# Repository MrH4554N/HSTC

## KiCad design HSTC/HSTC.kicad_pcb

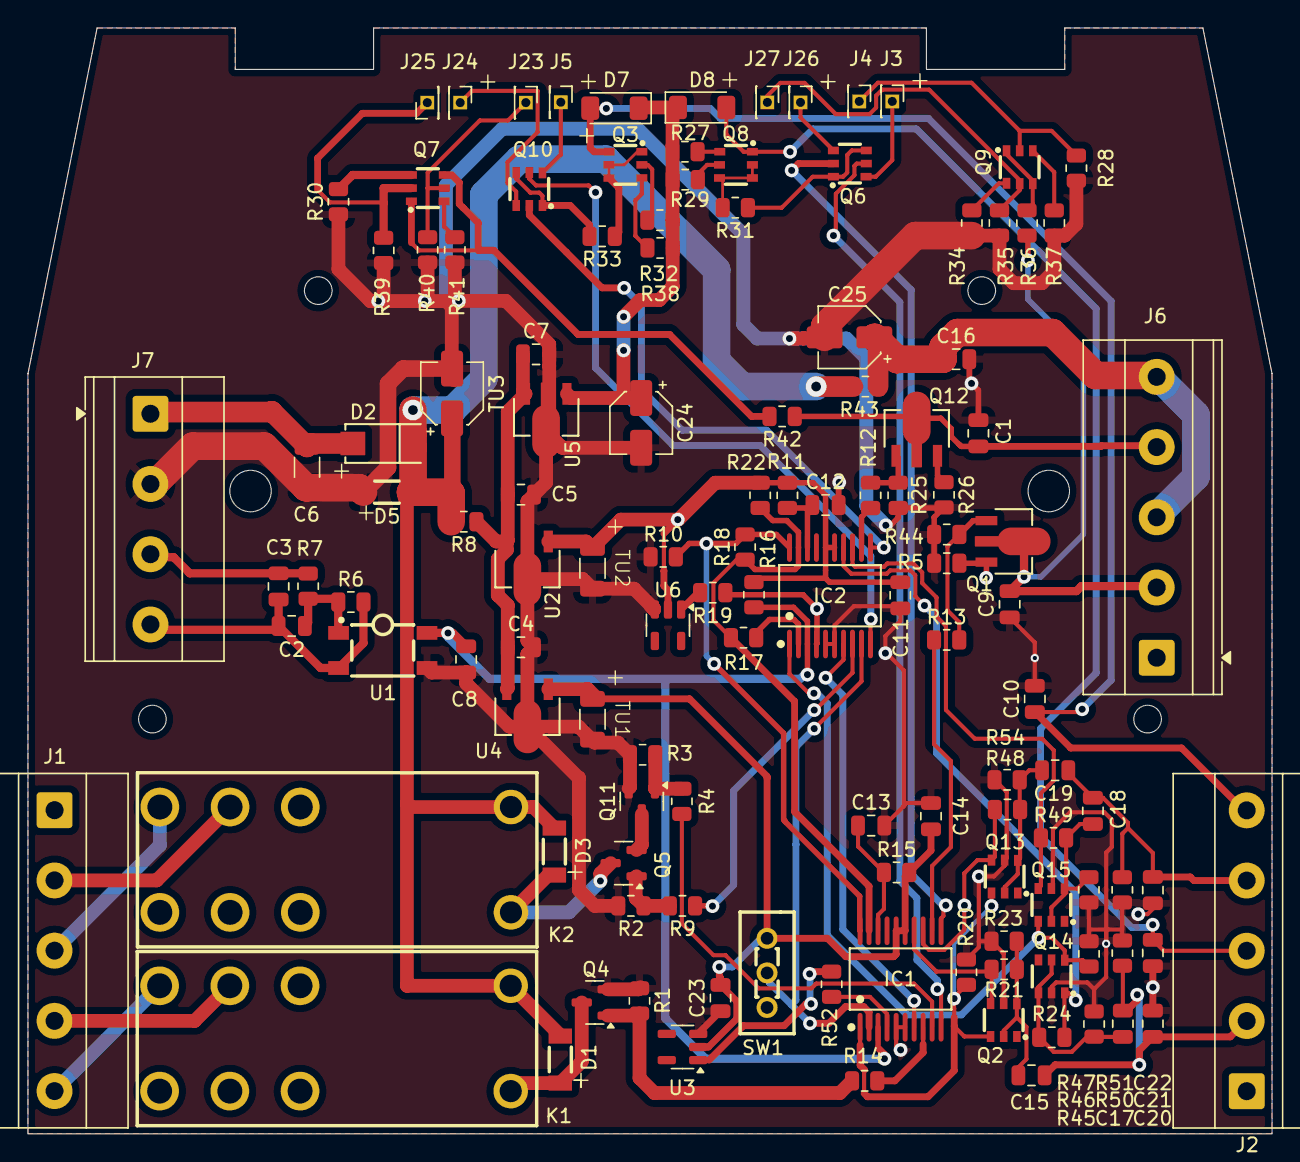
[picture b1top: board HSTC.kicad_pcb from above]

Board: 2 copper layers, 90.0 x 80.0 mm, 125 parts (0 on the bottom side), 84 nets.

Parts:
C1, C2, C4, C5, C7, C9, C10, C15, C16, C18, C19, C20, C21, C22, C23: 50V 1.5nF; C_0805_2012Metric
C3, C17: 50V 68nF ceramic; C_0805_2012Metric
C6: 50V 10nF ceramic; C_1206_3216Metric
C8, C11, C14: 50V 10nF; C_0805_2012Metric
C12, C13: 50V 68pF; C_0805_2012Metric
C24, C25: 2.2uF 35V; CP_Elec_4x5.4
D1, D3, D5: ZMM36_C8082 35V; LL-34_L3.5-W1.5-RD
D2: 1N4007G; SMA_L4.4-W2.6-LS5.0-RD
D7, D8: ZMM15_C179550 15V; D_MiniMELF
IC1, IC2: PIC16C620A-04/SS; SSOP-20_L7.2-W5.3-P0.65-LS7.8-BL
J1, J2, J6: Screw_Terminal_01x05; TerminalBlock_Phoenix_MKDS-1,5-5-5.08_1x05_P5.08mm_Horizont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
J3, J4, J5, J23, J24, J25, J26, J27: Conn_01x01_Pin; PinHeader_1x01_P1.27mm_Vertical
J7: Screw_Terminal_01x04; TerminalBlock_Phoenix_MKDS-1,5-4-5.08_1x04_P5.08mm_Horizont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
K1, K2: SMI-24VDC-SL-2C; RELAY-TH_SMI-X-XX-2C
Q1, Q12: BCX56; SOT-89-3_L4.5-W2.5-P1.50-LS4.2-BR
Q2, Q3, Q6, Q7, Q8, Q9, Q10, Q13, Q14, Q15: IMX1T110; SOT-457_L2.9-W1.6-P0.95-LS2.80-BR
Q4, Q5, Q11: BC846; SOT-23
R1, R4, R9, R12, R13, R14, R19, R52: 1k; R_0805_2012Metric
R2, R3: 4.7k; R_0805_2012Metric
R5, R26, R43: 4.7R; R_0805_2012Metric
R6, R10: 33k; R_0805_2012Metric
R7, R11, R15: 3.3k; R_0805_2012Metric
R8, R27, R29, R32, R38: 10R; R_0805_2012Metric
R16, R20, R22, R46: 10k; R_0805_2012Metric
R17, R18, R25, R44: 47k; R_0805_2012Metric
R21, R24, R48, R49: 100k; R_0805_2012Metric
R23, R45, R47, R54: 27k; R_0805_2012Metric
R28, R40: 330R; R_0805_2012Metric
R30, R31, R33, R34: 100R; R_0805_2012Metric
R35, R39: 150R; R_0805_2012Metric
R36, R42: 470R; R_0805_2012Metric
R37, R41, R50, R51: 270R; R_0805_2012Metric
SW1: SS12D00G4; SW-TH_SS-12D01-GX
TU1, TU2: 10uF 16V; Capacitor_Tantalum_1206x3216
TU3: 3.3uF 50V; CP_Elec_4x5.4
U1: TLP181GB-S; SOP-4_L3.7-W4.6-P2.54-LS7.0-TL
U2, U4: L78L05ABUTR; SOT-89-3_L4.5-W2.5-P1.50-LS4.2-TL
U3, U6: 5to5V; SOT-23-5
U5: 78L15_C5692991; SOT-89-3_L4.3-W2.3-P1.50-LS4.3-BR

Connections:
+24V: C6.1, D2.2 (A), J7.1
GND: C1.2, C4.2, C5.2, C6.2, C7.2, C8.2, C9.1, C10.2, C11.2, C12.2, C13.2, C14.1, C16.2, C20.1, C21.2, C22.2, C23.1, C24.2, C25.2, D5.2 (A), IC1.5 (VSS), IC1.6 (VSS), IC2.5 (VSS), IC2.6 (VSS), J7.2, Q2.5 (B1), Q4.2 (E), Q11.2 (E), Q13.5 (B1), Q14.2 (B2), Q15.5 (B1), R1.2, R2.2, R3.2, R5.1, R10.1, R20.1, R23.1, R25.2, R26.2, R28.1, R30.1, R34.2, R35.1, R37.1, R39.1, R40.1, R41.1, R44.2, R45.2, R46.1, R47.1, R50.2, R51.1, R54.2, SW1.1, TU1.2, TU2.2, TU3.2, U1.4 (EMI), U2.2 (GND), U3.3 (GND), U4.2 (GND), U5.2 (GND), U6.3 (GND)
unnamed: D1.2 (A), K1.8, Q4.3 (C)
unnamed: D1.1 (C), D2.1 (C), D3.1 (C), D5.1 (C), K1.1, K2.1, R8.2, R43.2, TU3.1
unnamed: D3.2 (A), K2.8, Q5.3 (C)
unnamed: C13.1, IC1.18 (OSC1/CLKIN), R15.1
unnamed: IC1.19 (RA0/AN0), IC2.19 (RA0/AN0), R17.1, R18.1, R22.2
unnamed: IC1.20 (RA1/AN1), IC2.20 (RA1/AN1), R10.2, R18.2
unnamed: IC1.1 (RA2/AN2/VREF), Q2.3 (E2), Q13.3 (E2), R20.2
unnamed: IC1.2 (RA3/AN3), IC2.9 (RB2), SW1.2
unnamed: C8.1, IC1.3 (RA4/T0CKI), IC2.3 (RA4/T0CKI), R16.2, U1.6 (COL)
unnamed: IC1.7 (RB0/INT), IC2.7 (RB0/INT)
unnamed: IC1.8 (RB1), R14.1
unnamed: IC1.9 (RB2), R4.1
unnamed: IC1.10 (RB3), Q6.5 (B1)
unnamed: IC1.11 (RB4), Q6.2 (B2)
unnamed: IC1.12 (RB5), R13.1
unnamed: IC1.13 (RB6), Q13.4 (C2), R48.1
unnamed: IC1.14 (RB7), Q2.4 (C2), R21.1
unnamed: IC1.4 (~MCLR/VPP), R52.1
unnamed: C12.1, IC2.18 (OSC1/CLKIN), R11.2
unnamed: IC2.1 (RA2/AN2/VREF), Q14.6 (E1), Q15.3 (E2), R46.2
unnamed: IC2.2 (RA3/AN3), R17.2
unnamed: IC2.8 (RB1), R9.1
unnamed: IC2.10 (RB3), Q10.5 (B1)
unnamed: IC2.11 (RB4), Q10.2 (B2)
unnamed: IC2.12 (RB5), R12.2
unnamed: IC2.13 (RB6), Q15.4 (C2), R49.1
unnamed: IC2.14 (RB7), Q14.1 (C1), R24.2
unnamed: IC2.4 (~MCLR/VPP), R19.2
unnamed: J1.2, K2.3
unnamed: J1.3, K2.4
unnamed: J1.4, K1.3
unnamed: J1.5, K1.4
unnamed: C15.1, C17.1, C20.2, J2.2, R50.1
unnamed: C21.1, D8.2, J2.3, Q8.1 (C1)
unnamed: C18.2, C19.1, C22.1, J2.4, R51.2
unnamed: C10.1, D7.2, J2.5, Q3.6 (E1)
unnamed: J3.1, Q6.6 (E1)
unnamed: J4.1, Q9.2 (B2), R28.2
unnamed: J5.1, Q10.6 (E1)
unnamed: C9.2, J6.2, Q1.2 (C), R36.2
unnamed: C16.1, C25.1, J6.3, J6.5, R43.1
unnamed: C1.1, J6.4, Q12.2 (C), R42.1
unnamed: C3.1, J7.3, R7.1
unnamed: C2.1, C3.2, J7.4, R6.2, U1.3 (CAT)
unnamed: J23.1, Q7.5 (B1), R40.2
unnamed: J24.1, Q10.3 (E2)
unnamed: J25.1, Q7.2 (B2), R39.2
unnamed: J26.1, Q6.3 (E2)
unnamed: J27.1, Q9.5 (B1), R35.2
unnamed: Q1.1 (B), R13.2, R44.1
unnamed: Q1.3 (E), R5.2
unnamed: C15.2, Q2.2 (B2), Q2.6 (E1), R21.2, R23.2
unnamed: Q3.1 (C1), Q3.4 (C2), Q3.5 (B1), R33.1
unnamed: Q3.2 (B2), R32.2
unnamed: Q3.3 (E2), R38.2
unnamed: Q4.1 (B), R1.1, R14.2
unnamed: Q5.1 (B), R2.1, R9.2
unnamed: Q6.1 (C1), Q6.4 (C2), R31.1
unnamed: Q7.1 (C1), Q7.4 (C2), R42.2
unnamed: Q7.6 (E1), R41.2
unnamed: Q7.3 (E2), R30.2
unnamed: Q8.5 (B1), R29.1
unnamed: Q8.2 (B2), Q8.3 (E2), Q8.4 (C2), R31.2
unnamed: Q8.6 (E1), R27.1
unnamed: Q9.1 (C1), Q9.4 (C2), R36.1
unnamed: Q9.6 (E1), R34.1
unnamed: Q9.3 (E2), R37.2
unnamed: Q10.1 (C1), Q10.4 (C2), R33.2
unnamed: Q11.1 (B), R3.1, R4.2
unnamed: Q5.2 (E), Q11.3 (C)
unnamed: Q12.1 (B), R12.1, R25.1
unnamed: Q12.3 (E), R26.1
unnamed: C19.2, Q13.2 (B2), Q13.6 (E1), R48.2, R54.1
unnamed: C17.2, Q14.3 (E2), Q14.5 (B1), R24.1, R45.1
unnamed: C18.1, Q15.2 (B2), Q15.6 (E1), R47.2, R49.2
unnamed: C2.2, R6.1, R7.2, U1.1 (AN)
unnamed: C4.1, C5.1, C7.1, R8.1, U2.3 (VIN), U4.3 (VIN), U5.3 (IN)
unnamed: C11.1, IC2.15 (VDD), IC2.16 (VDD), R11.1, R16.1, R22.1, TU2.1, U2.1 (VOUT), U6.2 (Vin)
unnamed: C14.2, C23.2, IC1.15 (VDD), IC1.16 (VDD), R15.2, SW1.3, TU1.1, U3.2 (Vin), U4.1 (VOUT)
unnamed: R52.2, U3.1 (Vout)
unnamed: C24.1, D7.1, D8.1, R27.2, R29.2, R32.1, R38.1, U5.1 (OUT)
unnamed: R19.1, U6.1 (Vout)

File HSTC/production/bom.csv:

Designator,Footprint,Quantity,Value,LCSC Part #
"C1, C10, C15, C16, C18, C19, C2, C20, C21, C22, C23, C4, C5, C7, C9",0805,15,50V 1.5nF,
"C11, C14, C8",0805,3,50V 10nF,
"C12, C13",0805,2,50V 68pF,
"C17, C3",0805,2,50V 68nF ceramic,
"C24, C25",CP_Elec_4x5.4,2,2.2uF 35V,
C6,1206,1,50V 10nF ceramic,
"D1, D3, D5",LL-34_L3.5-W1.5-RD,3,ZMM36_C8082 35V,C8082
D2,SMA_L4.4-W2.6-LS5.0-RD,1,1N4007G,C111122
"D7, D8",D_MiniMELF,2,ZMM15_C179550 15V,C179550
"IC1, IC2",SSOP-20_L7.2-W5.3-P0.65-LS7.8-BL,2,PIC16C620A-04/SS,C639116
"J1, J2, J6","TerminalBlock_Phoenix_MKDS-1,5-5-5.08_1x05_P5.08mm_Horizontal",3,Screw_Terminal_01x05,
"J23, J24, J25, J26, J27, J3, J4, J5",PinHeader_1x01_P1.27mm_Vertical,8,Conn_01x01_Pin,
J7,"TerminalBlock_Phoenix_MKDS-1,5-4-5.08_1x04_P5.08mm_Horizontal",1,Screw_Terminal_01x04,
"K1, K2",RELAY-TH_SMI-X-XX-2C,2,SMI-24VDC-SL-2C,C34457
"Q1, Q12",SOT-89-3_L4.5-W2.5-P1.50-LS4.2-BR,2,BCX56,C24280
"Q10, Q13, Q14, Q15, Q2, Q3, Q6, Q7, Q8, Q9",SOT-457_L2.9-W1.6-P0.95-LS2.80-BR,10,IMX1T110,C509893
"Q11, Q4, Q5",SOT-23,3,BC846,
"R1, R12, R13, R14, R19, R4, R52, R9",0805,8,1k,
"R10, R6",0805,2,33k,
"R11, R15, R7",0805,3,3.3k,
"R16, R20, R22, R46",0805,4,10k,
"R17, R18, R25, R44",0805,4,47k,
"R2, R3",0805,2,4.7k,
"R21, R24, R48, R49",0805,4,100k,
"R23, R45, R47, R54",0805,4,27k,
"R26, R43, R5",0805,3,4.7R,
"R27, R29, R32, R38, R8",0805,5,10R,
"R28, R40",0805,2,330R,
"R30, R31, R33, R34",0805,4,100R,
"R35, R39",0805,2,150R,
"R36, R42",0805,2,470R,
"R37, R41, R50, R51",0805,4,270R,
SW1,SW-TH_SS-12D01-GX,1,SS-12D01-G4,C698217
"TU1, TU2",Capacitor_Tantalum_1206x3216,2,10uF 16V,C7171
TU3,CP_Elec_4x5.4,1,3.3uF 50V,C7201
U1,SOP-4_L3.7-W4.6-P2.54-LS7.0-TL,1,TLP181GB-S,C388374
"U2, U4",SOT-89-3_L4.5-W2.5-P1.50-LS4.2-TL,2,L78L05ABUTR,C42738
"U3, U6",SOT-23-5,2,5to5V,
U5,SOT-89-3_L4.3-W2.3-P1.50-LS4.3-BR,1,78L15_C5692991,C5692991

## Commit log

2025-10-14 14/10/25
2025-10-14 Add files via upload
    14/10/25
2025-10-15 15/10/25
2025-10-28 28/10/25
